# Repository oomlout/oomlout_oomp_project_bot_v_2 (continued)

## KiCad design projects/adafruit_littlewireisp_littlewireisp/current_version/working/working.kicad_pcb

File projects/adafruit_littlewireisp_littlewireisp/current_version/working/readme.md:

# littlewireisp
 
## summary 
* id: adafruit_littlewireisp_littlewireisp
* user: adafruit
* name: littlewireisp
* board: littlewireisp
* repo: https://github.com/adafruit/LittleWireISP

* src_file_repo_sch: 
* src_file_repo_sch_link: https://github.com/adafruit/LittleWireISP/tree/master/
* full details link: https://github.com/oomlout/oomlout_oomp_project_bot_v_2/tree/main/projects/adafruit_littlewireisp_littlewireisp/current_version/working  

## schematic  
  
[schematic (pdf)](working_schematic.pdf) 

## pcb  

[board (pdf)](working.pdf)  

## working_bom
| Id | Designator | Footprint | Quantity | Designation | Supplier and ref |  | None | 
| --- | --- | --- | --- | --- | --- | --- | --- | 
| 1 | U2 | SOIC14 | 1 | 74AHC125-SOIC14 |  |  | [''] | 
| 2 | R2,R1 | 0603-NO | 2 | 68R |  |  | [''] | 
| 3 | R5 | 0603-NO | 1 | 10K |  |  | [''] | 
| 4 | C2,C3 | 0805-NO | 2 | 100n |  |  | [''] | 
| 5 | C1 | 0805-NO | 1 | 4u7 |  |  | [''] | 
| 6 | D4,D5 | CHIPLED_0805_NOOUTLINE | 2 |  |  |  | [''] | 
| 7 | R6,R4 | 0603-NO | 2 | 470R |  |  | [''] | 
| 8 | D2,D1 | SOD-323 | 2 | 3V6 |  |  | [''] | 
| 9 | D3 | SOD-123 | 1 |  |  |  | [''] | 
| 10 | X1 | USB-MINIB_LARGER | 1 |  |  |  | [''] | 
| 11 | R3 | 0603-NO | 1 | 1K5 |  |  | [''] | 
| 12 | R7 | 0603-NO | 1 | 1K |  |  | [''] | 
| 13 | U1 | SO08-EIAJ | 1 | ATTINY45 |  |  | [''] | 
| 14 | X2 | 2X3_SMD | 1 | AVR ISP |  |  | [''] | 

## bom_schematic
| Ref | Qnty | Value | Cmp name | Footprint | Description | Vendor | DNP | 
| --- | --- | --- | --- | --- | --- | --- | --- | 
| C1 | 1 | 4u7 | CAP_CERAMIC0805-NOOUTLINE | working:0805-NO |  |  |  | 
| C2, C3 | 2 | 100n | CAP_CERAMIC0805-NOOUTLINE | working:0805-NO |  |  |  | 
| D1, D2 | 2 | 3V6 | DIODE-ZENERSOD323 | working:SOD-323 |  |  |  | 
| D3 | 1 | DIODESOD-123 | DIODESOD-123 | working:SOD-123 |  |  |  | 
| D4, D5 | 2 | LED0805_NOOUTLINE | LED0805_NOOUTLINE | working:CHIPLED_0805_NOOUTLINE |  |  |  | 
| R1, R2 | 2 | 68R | RESISTOR_0603_NOOUT | working:0603-NO |  |  |  | 
| R3 | 1 | 1K5 | RESISTOR_0603_NOOUT | working:0603-NO |  |  |  | 
| R4, R6 | 2 | 470R | RESISTOR_0603_NOOUT | working:0603-NO |  |  |  | 
| R5 | 1 | 10K | RESISTOR_0603_NOOUT | working:0603-NO |  |  |  | 
| R7 | 1 | 1K | RESISTOR_0603_NOOUT | working:0603-NO |  |  |  | 
| U1 | 1 | ATTINY45 | ATTINY45 | working:SO08-EIAJ |  |  |  | 
| U2 | 1 | 74125-SOIC14 | 74125-SOIC14 | working:SOIC14 |  |  |  | 
| X1 | 1 | USBMINIBLARGE | USBMINIBLARGE | working:USB-MINIB_LARGER |  |  |  | 
| X2 | 1 | AVR_SPI_PRG_6SMD | AVR_SPI_PRG_6SMD | working:2X3_SMD |  |  |  |

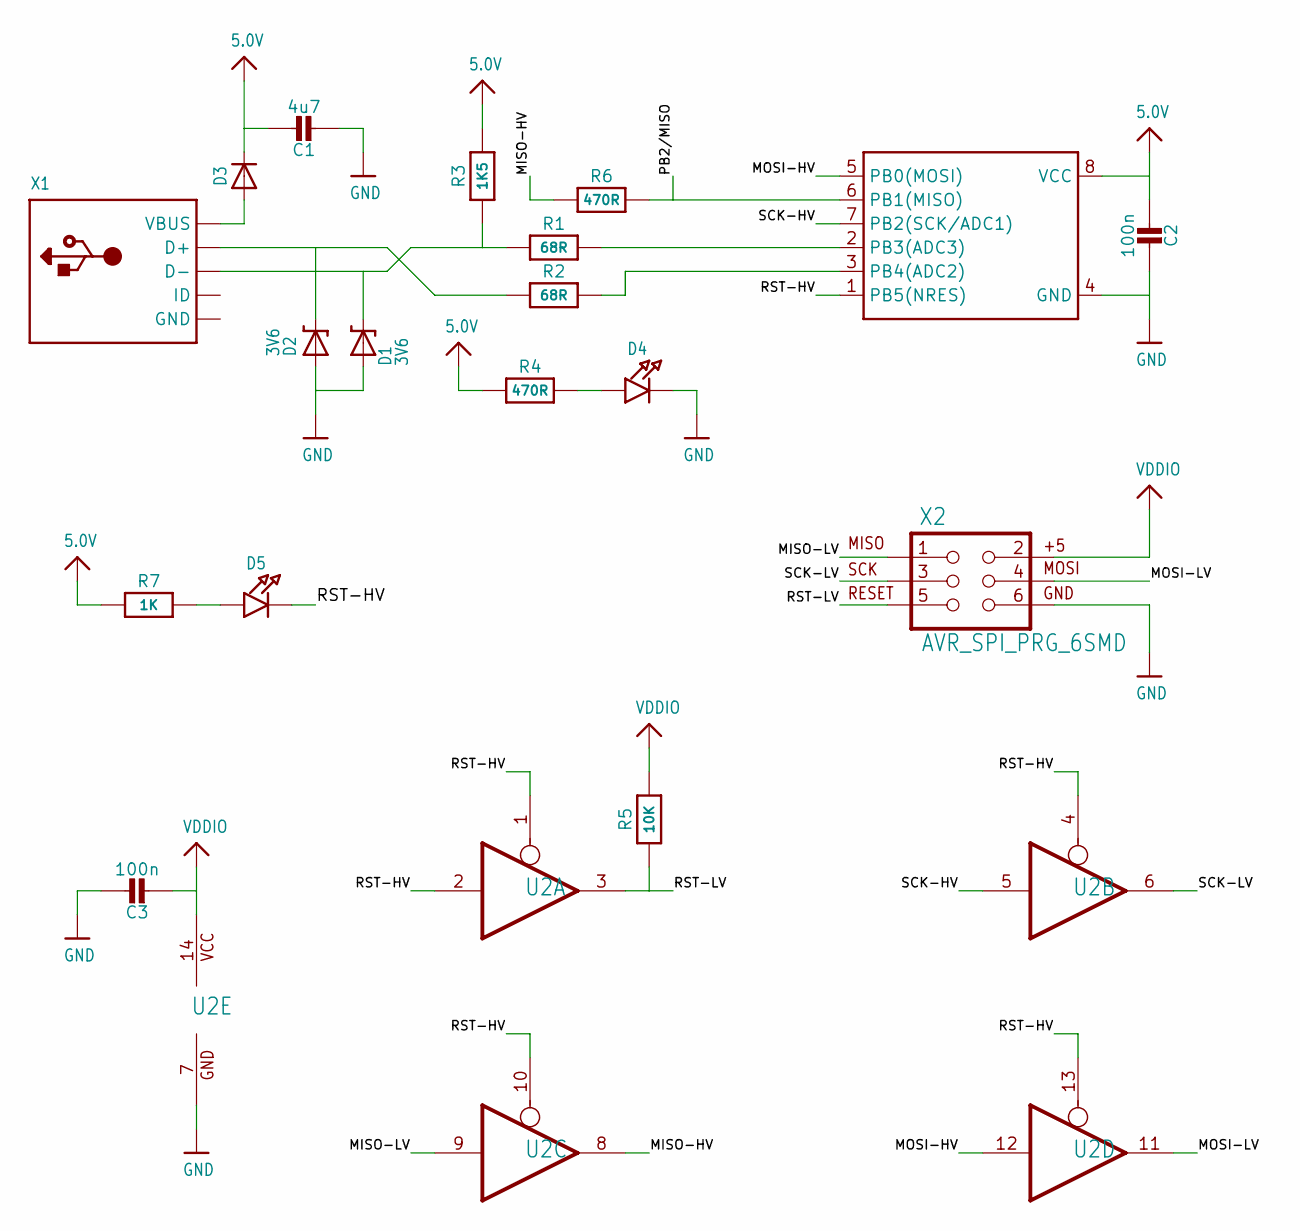
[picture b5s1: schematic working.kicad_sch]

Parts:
C1: 4u7; 0805-NO
C2, C3: 100n; 0805-NO
D1, D2: 3V6; SOD-323
D3: DIODESOD-123; SOD-123
D4, D5: LED0805_NOOUTLINE; CHIPLED_0805_NOOUTLINE
R1, R2: 68R; 0603-NO
R3: 1K5; 0603-NO
R4, R6: 470R; 0603-NO
R5: 10K; 0603-NO
R7: 1K; 0603-NO
U1: ATTINY45; SO08-EIAJ
U2: 74125-SOIC14; SOIC14
X1: USBMINIBLARGE; USB-MINIB_LARGER
X2: AVR_SPI_PRG_6SMD; 2X3_SMD

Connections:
5.0V: C1.1, C2.2, D3.C, R3.2, R4.1, R7.1, U1.8 (VCC)
MISO-HV: R6.1, U2.8 (O)
MISO-LV: U2.9 (I), X2.1
MOSI-HV: U1.5 (PB0(MOSI)), U2.12 (I)
MOSI-LV: U2.11 (O), X2.4
unnamed: D1.C, R1.1, R3.1, X1.D-
unnamed: D2.C, R2.1, X1.D+
unnamed: D5.A, R7.2
unnamed: R1.2, U1.2 (PB3(ADC3))
unnamed: R2.2, U1.3 (PB4(ADC2))
unnamed: D3.A, X1.VBUS
unnamed: D4.A, R4.2
PB2/MISO: R6.2, U1.6 (PB1(MISO))
RST-HV: D5.C, U1.1 (PB5(NRES)), U2.1 (OE), U2.2 (I), U2.4 (OE), U2.10 (OE), U2.13 (OE)
RST-LV: R5.1, U2.3 (O), X2.5
SCK-HV: U1.7 (PB2(SCK/ADC1)), U2.5 (I)
SCK-LV: U2.6 (O), X2.3
VDDIO: C3.2, R5.2, U2.14 (VCC), X2.2

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
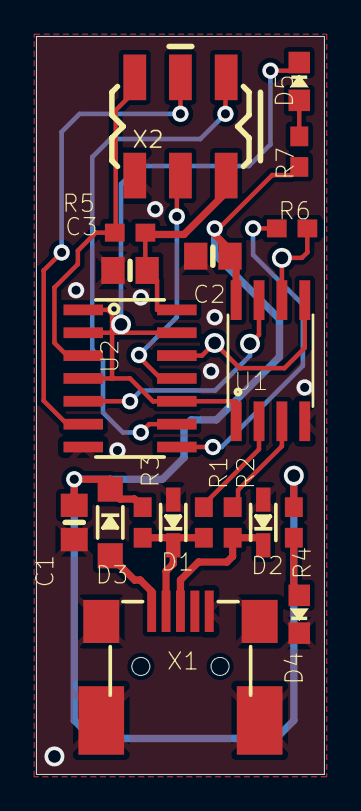
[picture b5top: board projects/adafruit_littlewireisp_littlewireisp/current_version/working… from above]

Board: 2 copper layers, 16.0 x 41.0 mm, 19 parts (0 on the bottom side), 19 nets.

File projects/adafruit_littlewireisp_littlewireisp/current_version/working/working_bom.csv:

"Id";"Designator";"Footprint";"Quantity";"Designation";"Supplier and ref";
1;"U2";"SOIC14";1;"74AHC125-SOIC14";;;
2;"R2,R1";"0603-NO";2;"68R";;;
3;"R5";"0603-NO";1;"10K";;;
4;"C2,C3";"0805-NO";2;"100n";;;
5;"C1";"0805-NO";1;"4u7";;;
6;"D4,D5";"CHIPLED_0805_NOOUTLINE";2;"";;;
7;"R6,R4";"0603-NO";2;"470R";;;
8;"D2,D1";"SOD-323";2;"3V6";;;
9;"D3";"SOD-123";1;"";;;
10;"X1";"USB-MINIB_LARGER";1;"";;;
11;"R3";"0603-NO";1;"1K5";;;
12;"R7";"0603-NO";1;"1K";;;
13;"U1";"SO08-EIAJ";1;"ATTINY45";;;
14;"X2";"2X3_SMD";1;"AVR ISP";;;

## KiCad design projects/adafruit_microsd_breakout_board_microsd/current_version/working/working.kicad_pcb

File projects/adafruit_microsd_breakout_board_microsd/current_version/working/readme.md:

# microsd_breakout_board
 
## summary 
* id: adafruit_microsd_breakout_board_microsd
* user: adafruit
* name: microsd_breakout_board
* board: microsd
* repo: https://github.com/adafruit/MicroSD-breakout-board

* src_file_repo_sch: 
* src_file_repo_sch_link: https://github.com/adafruit/MicroSD-breakout-board/tree/master/
* full details link: https://github.com/oomlout/oomlout_oomp_project_bot_v_2/tree/main/projects/adafruit_microsd_breakout_board_microsd/current_version/working  

## schematic  
  
[schematic (pdf)](working_schematic.pdf) 

## pcb  

[board (pdf)](working.pdf)  

## working_bom
| Id | Designator | Footprint | Quantity | Designation | Supplier and ref |  | None | 
| --- | --- | --- | --- | --- | --- | --- | --- | 
| 1 | @HOLE2,@HOLE1,@HOLE3,@HOLE0 |  | 4 |  |  |  | [''] | 
| 2 | IC1 | SO16 | 1 | 4050D |  |  | [''] | 
| 3 | C1 | A_3216-18R | 1 | 10uF/10V |  |  | [''] | 
| 4 | U$2,U$1 | FIDUCIAL_1MM | 2 | FIDUCIAL |  |  | [''] | 
| 5 | IC2 | SOT23-5L | 1 | LP298XS |  |  | [''] | 
| 6 | R1 | R0805 | 1 | 1K |  |  | [''] | 
| 7 | ACT0 | CHIP-LED0805 | 1 | RED |  |  | [''] | 
| 8 | JP1 | 1X08-BIG | 1 |  |  |  | [''] | 
| 9 | X1 | MICROSD | 1 | MICROSD |  |  | [''] | 
| 10 | C2 | C0805K | 1 | 0.1uF |  |  | [''] | 

## bom_schematic
| Ref | Qnty | Value | Cmp name | Footprint | Description | Vendor | DNP | 
| --- | --- | --- | --- | --- | --- | --- | --- | 
| ACT0 | 1 | RED | LEDCHIP-LED0805 | working:CHIP-LED0805 |  |  |  | 
| C1 | 1 | 10uF/10V | CPOL-USA/3216-18R | working:A_3216-18R |  |  |  | 
| C2 | 1 | 0.1uF | C-USC0805K | working:C0805K |  |  |  | 
| IC1 | 1 | 4050D | 4050D | working:SO16 |  |  |  | 
| IC2 | 1 | LP298XS | LP298XS | working:SOT23-5L |  |  |  | 
| JP1 | 1 | PINHD-1X8BIG | PINHD-1X8BIG | working:1X08-BIG |  |  |  | 
| R1 | 1 | 1K | R-US_R0805 | working:R0805 |  |  |  | 
| U$1, U$2 | 2 | FIDUCIAL | FIDUCIAL | working:FIDUCIAL_1MM |  |  |  | 
| X1 | 1 | MICROSD | MICROSD | working:MICROSD |  |  |  |

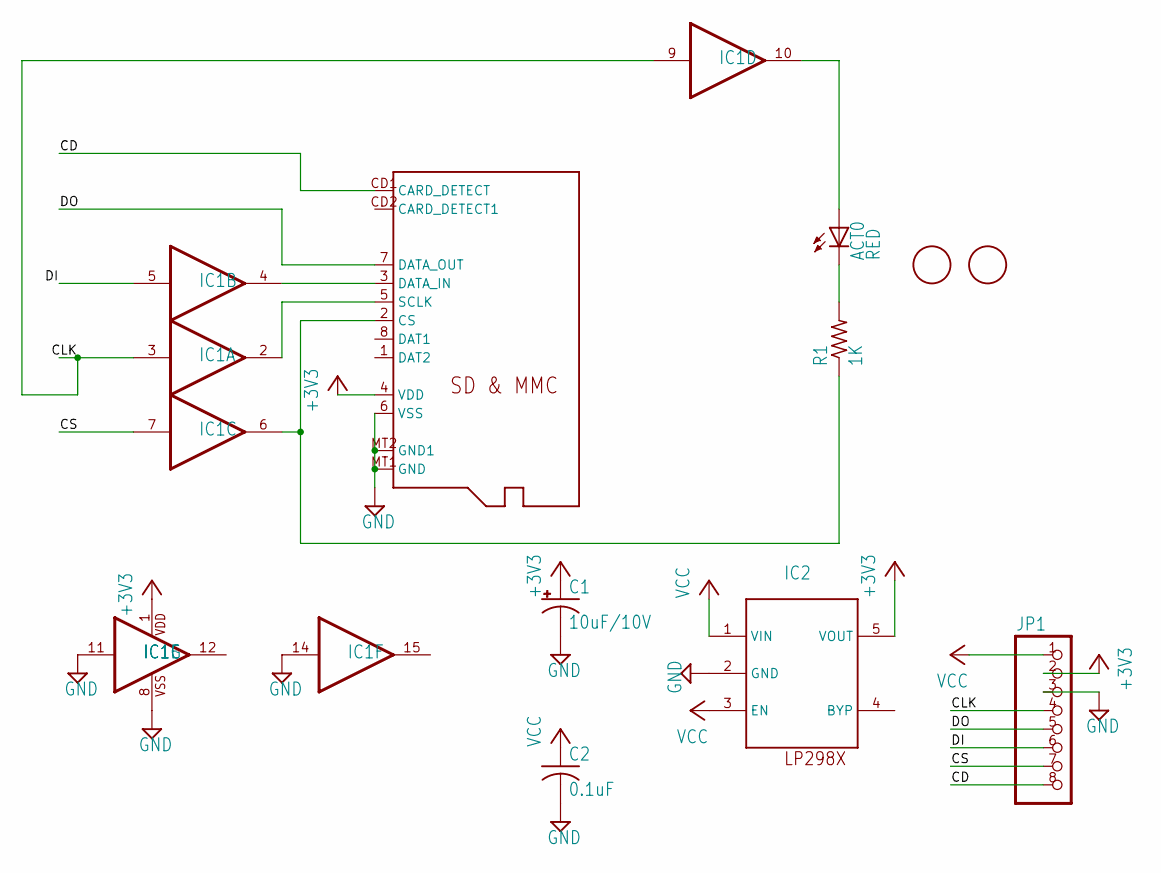
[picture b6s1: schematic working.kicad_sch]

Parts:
ACT0: RED; CHIP-LED0805
C1: 10uF/10V; A_3216-18R
C2: 0.1uF; C0805K
IC1: 4050D; SO16
IC2: LP298XS; SOT23-5L
JP1: PINHD-1X8BIG; 1X08-BIG
R1: 1K; R0805
U$1, U$2: FIDUCIAL; FIDUCIAL_1MM
X1: MICROSD

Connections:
+3V3: C1.+, IC1.1 (VDD), IC2.5 (VOUT), JP1.2, X1.4 (VDD)
CD: JP1.8, X1.CD1 (CARD_DETECT)
CLK: IC1.3 (I), IC1.9 (I), JP1.4
CS: IC1.7 (I), JP1.7
DI: IC1.5 (I), JP1.6
DO: JP1.5, X1.7 (DATA_OUT)
GND: C1.-, C2.2, IC1.8 (VSS), IC1.11 (I), IC1.14 (I), IC2.2 (GND), JP1.3, X1.6 (VSS), X1.MT1 (GND), X1.MT2 (GND1)
unnamed: ACT0.A, IC1.10 (O)
unnamed: IC1.2 (O), X1.5 (SCLK)
unnamed: IC1.6 (O), R1.1, X1.2 (CS)
unnamed: ACT0.C, R1.2
unnamed: IC1.4 (O), X1.3 (DATA_IN)
VCC: C2.1, IC2.1 (VIN), IC2.3 (EN), JP1.1

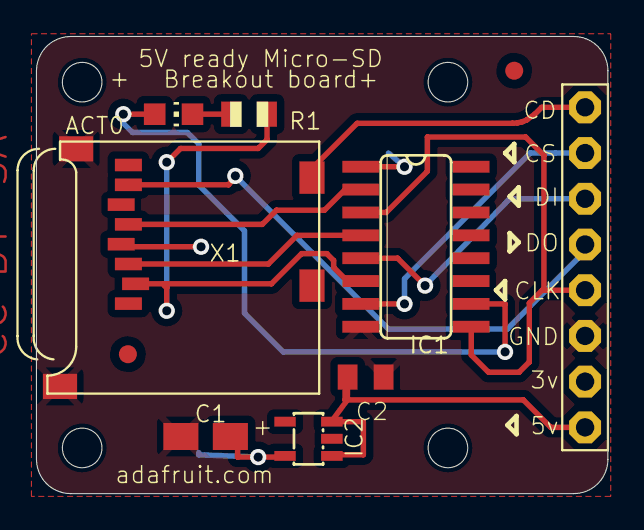
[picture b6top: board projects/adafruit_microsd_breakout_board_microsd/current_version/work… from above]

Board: 16 copper layers, 31.8 x 25.4 mm, 14 parts (0 on the bottom side), 13 nets.

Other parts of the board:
@HOLE0, @HOLE1, @HOLE2, @HOLE3: (no value)

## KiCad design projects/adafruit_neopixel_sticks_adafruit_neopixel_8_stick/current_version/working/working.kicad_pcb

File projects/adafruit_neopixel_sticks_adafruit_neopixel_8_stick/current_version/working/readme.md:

# neopixel_sticks
 
## summary 
* id: adafruit_neopixel_sticks_adafruit_neopixel_8_stick
* user: adafruit
* name: neopixel_sticks
* board: adafruit_neopixel_8_stick
* repo: https://github.com/adafruit/NeoPixel-Sticks

* src_file_repo_sch: 
* src_file_repo_sch_link: https://github.com/adafruit/NeoPixel-Sticks/tree/master/
* full details link: https://github.com/oomlout/oomlout_oomp_project_bot_v_2/tree/main/projects/adafruit_neopixel_sticks_adafruit_neopixel_8_stick/current_version/working  

## schematic  
  
[schematic (pdf)](working_schematic.pdf) 

## pcb  

[board (pdf)](working.pdf)  

## working_bom
| Id | Designator | Footprint | Quantity | Designation | Supplier and ref |  | None | 
| --- | --- | --- | --- | --- | --- | --- | --- | 
| 1 | C7,C4,C1,C5,C3,C2,C6 | C0805K | 7 |  |  |  | [''] | 
| 2 | LED2,LED1,LED7,LED4,LED8,LED5,LED6,LED3 | WS2812B-NARROW | 8 | WS2812B5050 |  |  | [''] | 
| 3 | FID1,FID3 | FIDUCIAL_1MM | 2 | FIDUCIAL" |  |  | [''] | 
| 4 | U$2,U$3 | MOUNTINGHOLE_2.0_PLATED | 2 | MOUNTINGHOLE2.0 |  |  | [''] | 
| 5 | R1 | _0805MP | 1 | 470 OHM, |  |  | [''] | 
| 6 | U$4 | ADAFRUIT_2.5MM | 1 |  |  |  | [''] | 
| 7 | U$1 | ADAFRUIT_TEXT_20MM | 1 |  |  |  | [''] | 
| 8 | CN2,CN1 | 1X4-SMT | 2 | 1X4SMT |  |  | [''] | 

## bom_schematic
| Ref | Qnty | Value | Cmp name | Footprint | Description | Vendor | DNP | 
| --- | --- | --- | --- | --- | --- | --- | --- | 
| C1, C2, C3, C4, C5, C6, C7 | 7 | C-USC0805K | C-USC0805K | working:C0805K |  |  |  | 
| CN1, CN2 | 2 | 1X4SMT | 1X4SMT | working:1X4-SMT |  |  |  | 
| FID1, FID3 | 2 | FIDUCIAL"" | FIDUCIAL{dblquote}{dblquote} | working:FIDUCIAL_1MM |  |  |  | 
| LED1, LED2, LED3, LED4, LED5, LED6, LED7, LED8 | 8 | WS2812B5050 | WS2812B5050 | working:WS2812B |  |  |  | 
| R1 | 1 | 470 OHM, | RESISTOR_0805MP | working:_0805MP |  |  |  | 
| U$2, U$3 | 2 | MOUNTINGHOLE2.0 | MOUNTINGHOLE2.0 | working:MOUNTINGHOLE_2.0_PLATED |  |  |  | 

## mounting_holes
| x | y | package | value | ref | size | 
| --- | --- | --- | --- | --- | --- | 
| 0.0 | 0.0 | MOUNTINGHOLE_2.0_PLATED | MOUNTINGHOLE2.0 | U$2 | m3 | 
| 25.4 | 0.0 | MOUNTINGHOLE_2.0_PLATED | MOUNTINGHOLE2.0 | U$3 | m3 |

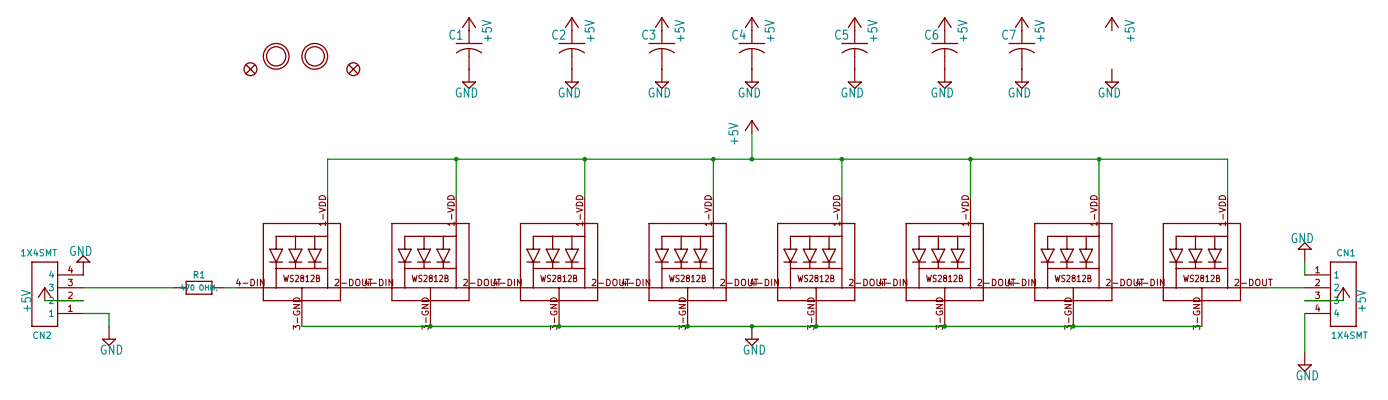
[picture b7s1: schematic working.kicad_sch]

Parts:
C1, C2, C3, C4, C5, C6, C7: C-USC0805K; C0805K
CN1, CN2: 1X4SMT; 1X4-SMT
FID1, FID3: FIDUCIAL""; FIDUCIAL_1MM
LED1, LED2, LED3, LED4, LED5, LED6, LED7, LED8: WS2812B5050; WS2812B
R1: 470 OHM,; _0805MP
U$2, U$3: MOUNTINGHOLE2.0; MOUNTINGHOLE_2.0_PLATED

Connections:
+5V: C1.1, C2.1, C3.1, C4.1, C5.1, C6.1, C7.1, CN1.3, CN2.2, LED1.1-VDD (VDD), LED2.1-VDD (VDD), LED3.1-VDD (VDD), LED4.1-VDD (VDD), LED5.1-VDD (VDD), LED6.1-VDD (VDD), LED7.1-VDD (VDD), LED8.1-VDD (VDD)
GND: C1.2, C2.2, C3.2, C4.2, C5.2, C6.2, C7.2, CN1.1, CN1.4, CN2.1, CN2.4, LED1.3-GND (GND), LED2.3-GND (GND), LED3.3-GND (GND), LED4.3-GND (GND), LED5.3-GND (GND), LED6.3-GND (GND), LED7.3-GND (GND), LED8.3-GND (GND)
unnamed: LED1.2-DOUT (DO), LED2.4-DIN (DI)
unnamed: LED2.2-DOUT (DO), LED3.4-DIN (DI)
unnamed: LED3.2-DOUT (DO), LED4.4-DIN (DI)
unnamed: LED4.2-DOUT (DO), LED5.4-DIN (DI)
unnamed: LED5.2-DOUT (DO), LED6.4-DIN (DI)
unnamed: LED6.2-DOUT (DO), LED7.4-DIN (DI)
unnamed: LED7.2-DOUT (DO), LED8.4-DIN (DI)
unnamed: CN2.3, R1.1
unnamed: CN1.2, LED8.2-DOUT (DO)
unnamed: LED1.4-DIN (DI), R1.2

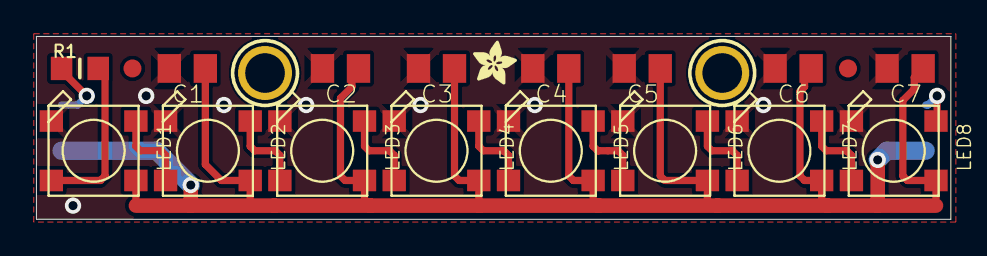
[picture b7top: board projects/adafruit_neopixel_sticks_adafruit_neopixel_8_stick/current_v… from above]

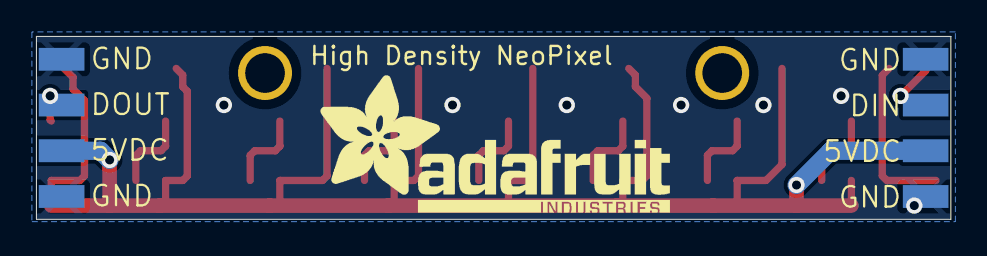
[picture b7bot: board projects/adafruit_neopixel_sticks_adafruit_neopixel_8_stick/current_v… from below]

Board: 2 copper layers, 50.8 x 10.2 mm, 24 parts (3 on the bottom side), 12 nets.

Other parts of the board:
U$1: ADAFRUIT_TEXT_20MM
U$4: ADAFRUIT_2.5MM
